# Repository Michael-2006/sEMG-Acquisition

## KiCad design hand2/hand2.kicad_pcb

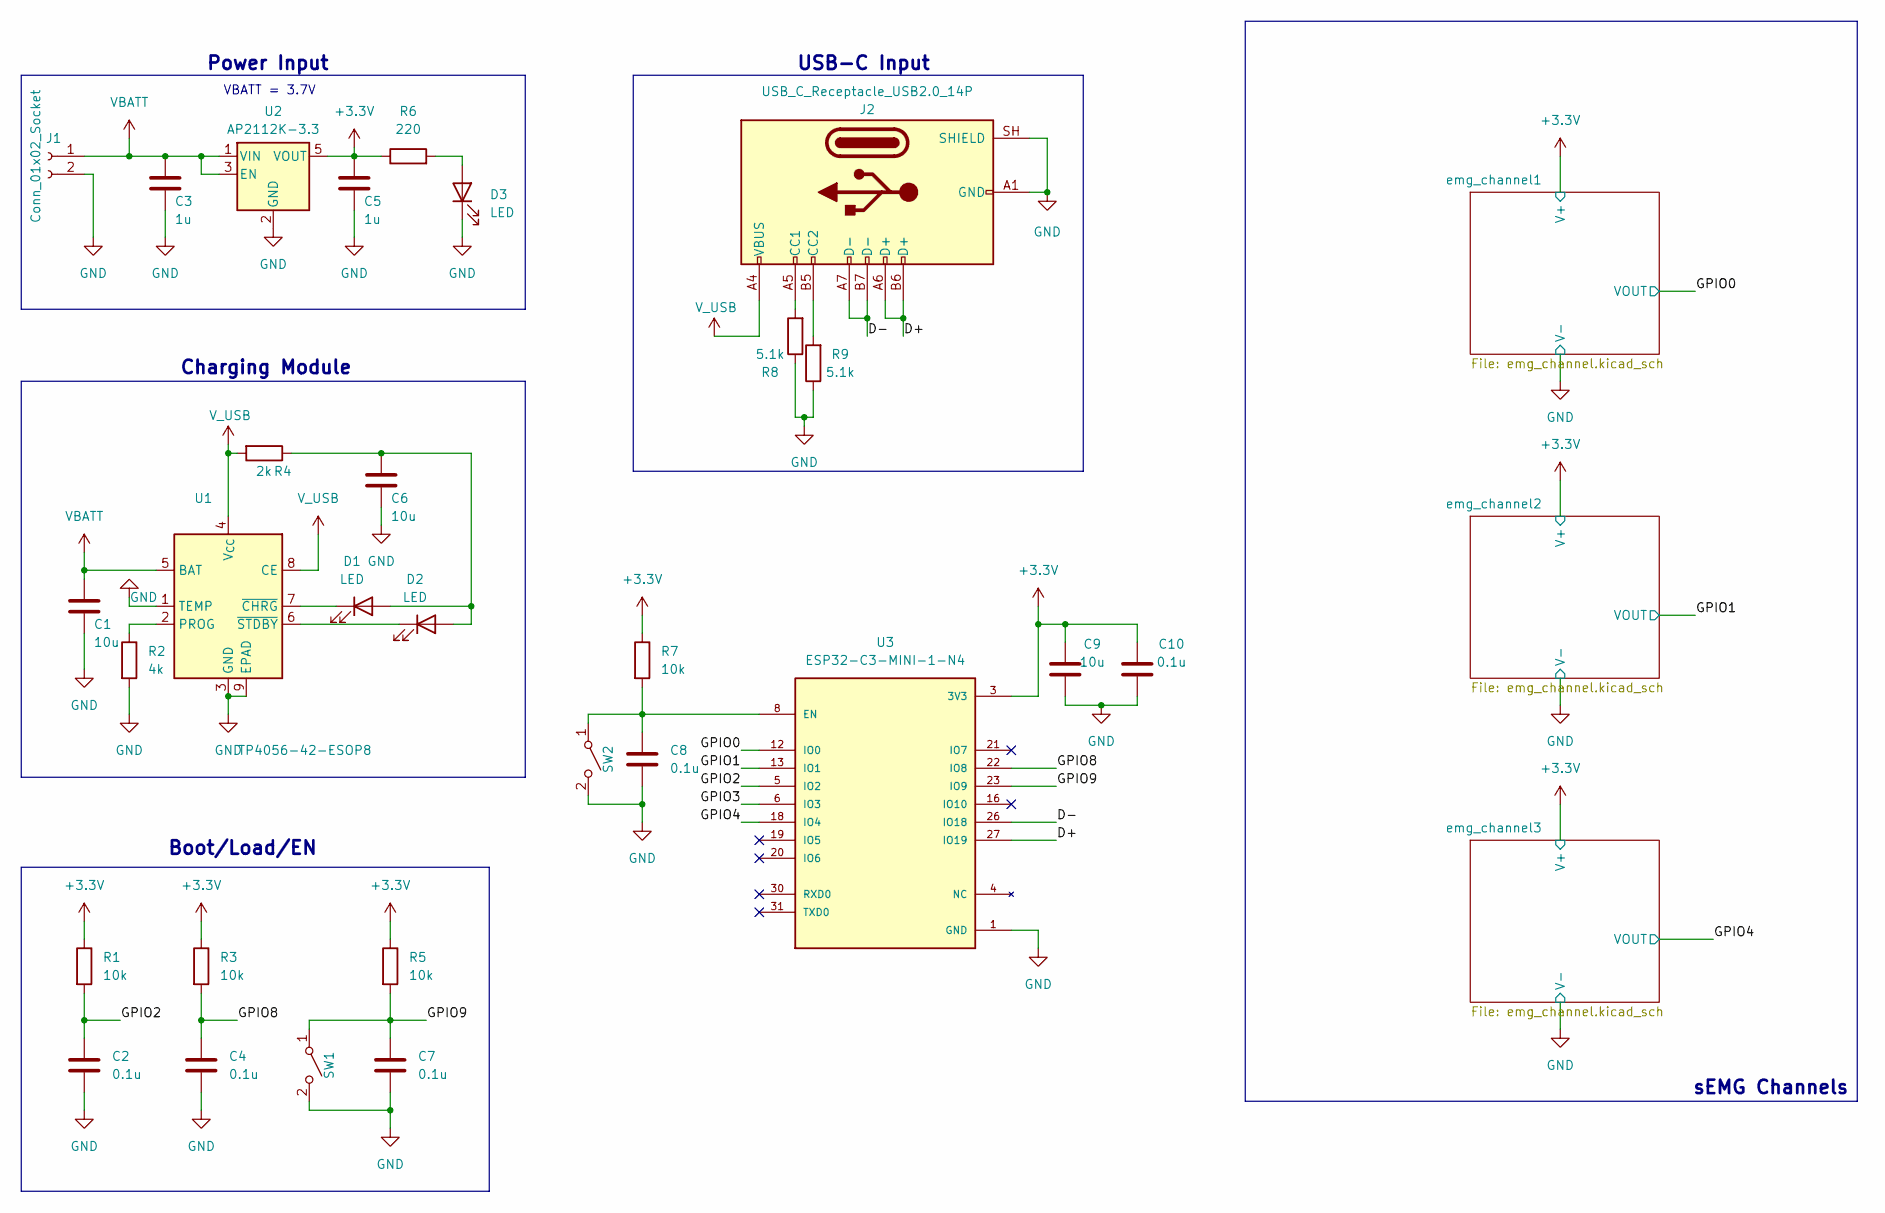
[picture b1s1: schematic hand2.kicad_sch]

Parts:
C1, C6, C9: 10u; C_0603_1608Metric_Pad1.08x0.95mm_HandSolder
C2, C4, C7, C8, C10: 0.1u; C_0603_1608Metric_Pad1.08x0.95mm_HandSolder
C3, C5: 1u; C_0603_1608Metric_Pad1.08x0.95mm_HandSolder
D1, D2, D3: LED; LED_0805_2012Metric_Pad1.15x1.40mm_HandSolder
J1: Conn_01x02_Socket; JST_PH_S2B-PH-SM4-TB_1x02-1MP_P2.00mm_Horizontal
J2: USB_C_Receptacle_USB2.0_14P; USB_C_Receptacle_HCTL_HC-TYPE-C-16P-01A
R1, R3, R5, R7: 10k; R_0603_1608Metric_Pad0.98x0.95mm_HandSolder
R2: 4k; R_0603_1608Metric_Pad0.98x0.95mm_HandSolder
R4: 2k; R_0603_1608Metric_Pad0.98x0.95mm_HandSolder
R6: 220; R_0603_1608Metric_Pad0.98x0.95mm_HandSolder
R8, R9: 5.1k; R_0603_1608Metric_Pad0.98x0.95mm_HandSolder
SW1, SW2: SW_SPST; SW_SPST_CK_RS282G05A3
U1: TP4056-42-ESOP8; SOIC-8-1EP_3.9x4.9mm_P1.27mm_EP2.41x3.3mm_ThermalVias
U2: AP2112K-3.3; SOT-23-5
U3: ESP32-C3-MINI-1-N4; XCVR_ESP32-C3-MINI-1-N4; PARTREV v1.0

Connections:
+3.3V: C5.1, C9.1, C10.2, R1.1, R3.1, R5.1, R6.1, R7.1, U2.5 (VOUT), U3.3 (3V3); also elsewhere on the board
/D+: J2.A6 (D+), J2.B6 (D+), U3.27 (IO19)
/D-: J2.A7 (D-), J2.B7 (D-), U3.26 (IO18)
/GPIO0: U3.12 (IO0); also elsewhere on the board
/GPIO1: U3.13 (IO1); also elsewhere on the board
/GPIO2: C2.1, R1.2, U3.5 (IO2)
/GPIO3: U3.6 (IO3)
/GPIO4: U3.18 (IO4); also elsewhere on the board
/GPIO8: C4.1, R3.2, U3.22 (IO8)
/GPIO9: C7.1, R5.2, SW1.1 (A), U3.23 (IO9)
unnamed: C6.1, D1.2 (A), D2.2 (A), R4.1
unnamed: D1.1 (K), U1.7 (~CHRG)
unnamed: D2.1 (K), U1.6 (~STDBY)
unnamed: D3.2 (A), R6.2
unnamed: J2.A5 (CC1), R8.2
unnamed: J2.B5 (CC2), R9.2
unnamed: C8.1, R7.2, SW2.1 (A), U3.8 (EN)
unnamed: R2.1, U1.2 (PROG)
VBATT: C1.1, C3.1, J1.1, U1.5 (BAT), U2.1 (VIN), U2.3 (EN)
V_USB: J2.A4 (VBUS), J2.A9 (VBUS), J2.B4 (VBUS), J2.B9 (VBUS), R4.2, U1.4 (V_{CC}), U1.8 (CE)

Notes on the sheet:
USB-C Input
VBATT = 3.7V
Power Input
Charging Module
Boot/Load/EN
sEMG Channels

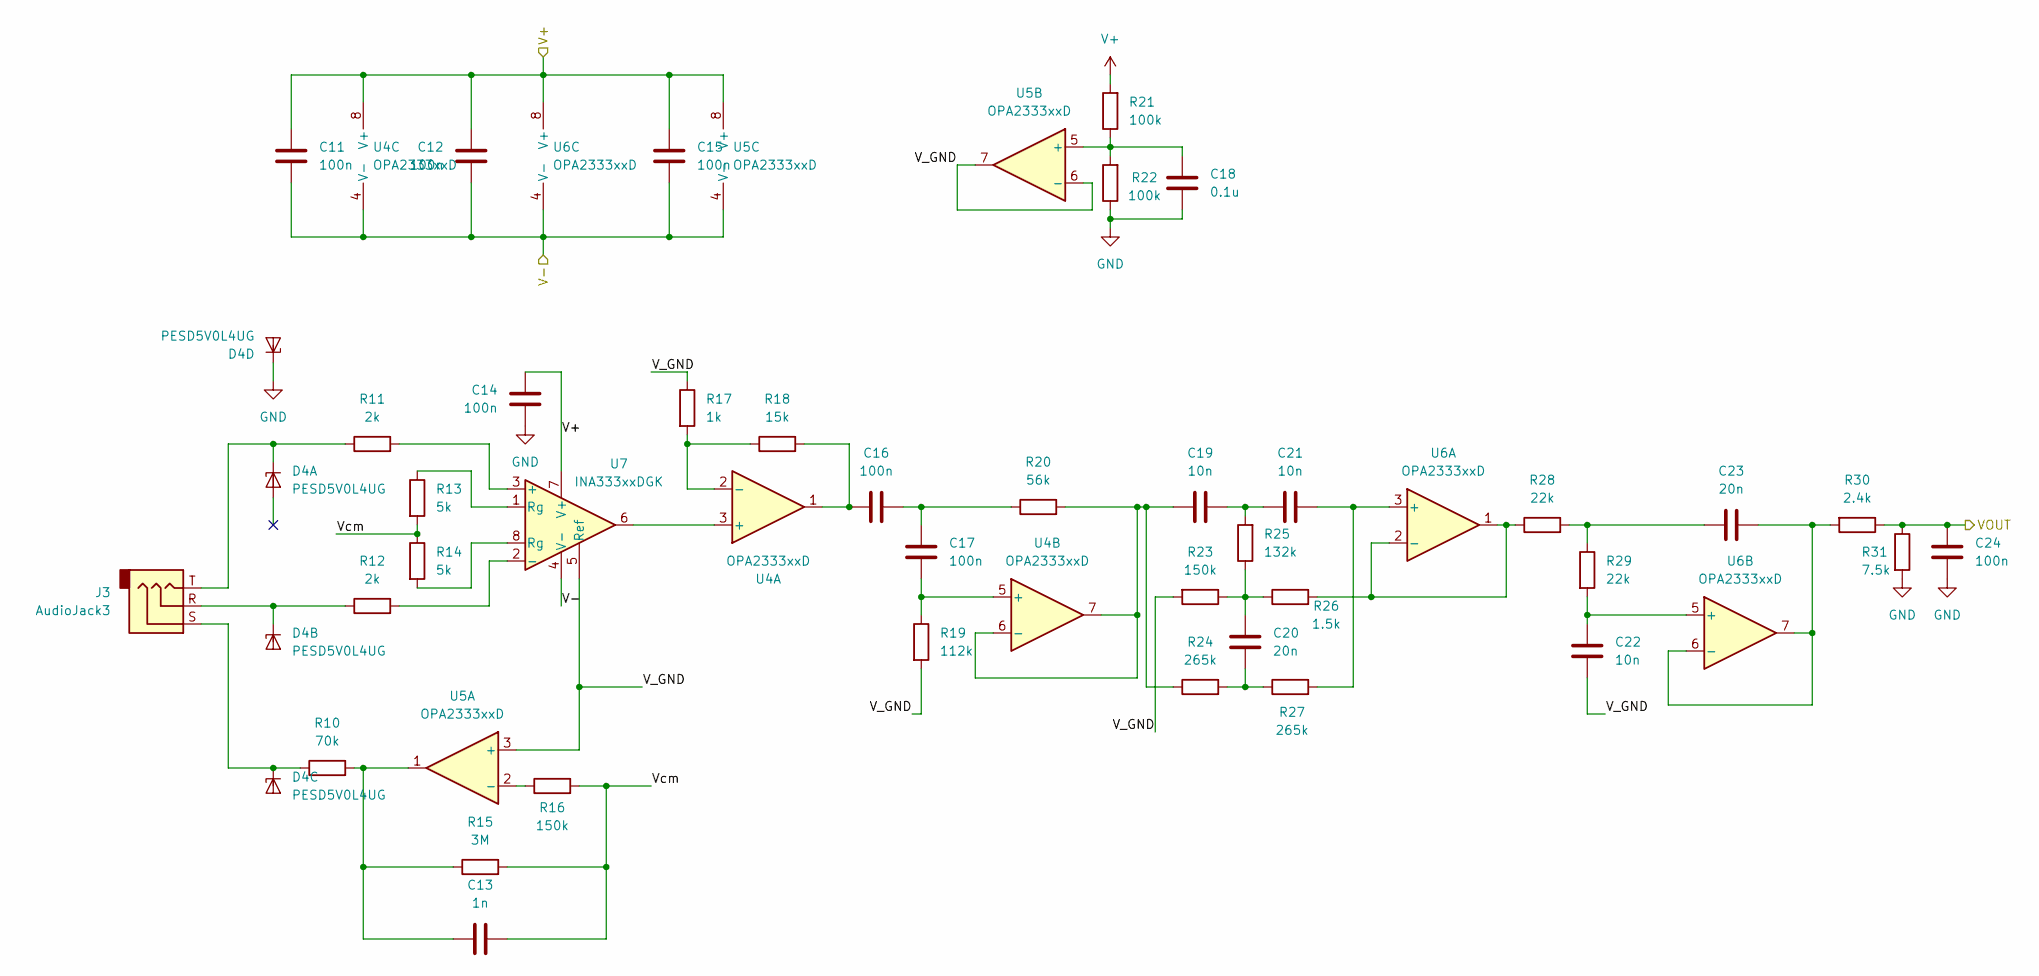
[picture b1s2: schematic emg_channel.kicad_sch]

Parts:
C11, C12, C14, C15, C16, C17, C24: 100n; C_0603_1608Metric_Pad1.08x0.95mm_HandSolder
C13: 1n; C_0603_1608Metric_Pad1.08x0.95mm_HandSolder
C18: 0.1u; C_0603_1608Metric_Pad1.08x0.95mm_HandSolder
C19, C21, C22: 10n; C_0603_1608Metric_Pad1.08x0.95mm_HandSolder
C20, C23: 20n; C_0603_1608Metric_Pad1.08x0.95mm_HandSolder
D4: PESD5V0L4UG; SOT-353_SC-70-5
J3: AudioJack3; Jack_3.5mm_CUI_SJ1-3533NG_Horizontal_CircularHoles
R10: 70k; R_0603_1608Metric_Pad0.98x0.95mm_HandSolder
R11, R12: 2k; R_0603_1608Metric_Pad0.98x0.95mm_HandSolder
R13, R14: 5k; R_0603_1608Metric_Pad0.98x0.95mm_HandSolder
R15: 3M; R_0603_1608Metric_Pad0.98x0.95mm_HandSolder
R16, R23: 150k; R_0603_1608Metric_Pad0.98x0.95mm_HandSolder
R17: 1k; R_0603_1608Metric_Pad0.98x0.95mm_HandSolder
R18: 15k; R_0603_1608Metric_Pad0.98x0.95mm_HandSolder
R19: 112k; R_0603_1608Metric_Pad0.98x0.95mm_HandSolder
R20: 56k; R_0603_1608Metric_Pad0.98x0.95mm_HandSolder
R21, R22: 100k; R_0603_1608Metric_Pad0.98x0.95mm_HandSolder
R24, R27: 265k; R_0603_1608Metric_Pad0.98x0.95mm_HandSolder
R25: 132k; R_0603_1608Metric_Pad0.98x0.95mm_HandSolder
R26: 1.5k; R_0603_1608Metric_Pad0.98x0.95mm_HandSolder
R28, R29: 22k; R_0603_1608Metric_Pad0.98x0.95mm_HandSolder
R30: 2.4k; R_0603_1608Metric_Pad0.98x0.95mm_HandSolder
R31: 7.5k; R_0603_1608Metric_Pad0.98x0.95mm_HandSolder
U4, U5, U6: OPA2333xxD; VSSOP-8_3x3mm_P0.65mm
U7: INA333xxDGK; VSSOP-8_3x3mm_P0.65mm

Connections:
+3.3V: C11.1, C12.1, C14.1, C15.1, R21.2, U4.8 (V+), U5.8 (V+), U6.8 (V+), U7.7 (V+); also elsewhere on the board
/GPIO0: C24.2, R30.1, R31.1; also elsewhere on the board
/emg_channel1/V_GND: C22.1, R17.1, R19.2, R23.2, U5.3 (+), U5.6 (-), U5.7, U7.5 (Ref)
/emg_channel1/Vcm: C13.1, R13.2, R14.1, R15.2, R16.2
unnamed: C13.2, R10.2, R15.1, U5.1
unnamed: C16.1, R18.2, U4.1
unnamed: C16.2, C17.1, R20.1
unnamed: C19.2, C21.1, R25.2
unnamed: C20.1, R24.2, R27.1
unnamed: C20.2, R23.1, R25.1, R26.1
unnamed: C23.1, R28.2, R29.1
unnamed: D4.1 (K1), J3.T, R11.1
unnamed: D4.3 (K2), J3.R, R12.1
unnamed: D4.4 (K3), J3.S, R10.1
unnamed: R13.1, U7.1 (Rg)
unnamed: R14.2, U7.8 (Rg)
unnamed: U4.3 (+), U7.6
unnamed: R17.2, R18.1, U4.2 (-)
unnamed: C17.2, R19.1, U4.5 (+)
unnamed: C19.1, R20.2, R24.1, U4.6 (-), U4.7
unnamed: R16.1, U5.2 (-)
unnamed: C18.1, R21.1, R22.2, U5.5 (+)
unnamed: C21.2, R27.2, U6.3 (+)
unnamed: R26.2, R28.1, U6.1, U6.2 (-)
unnamed: C22.2, R29.2, U6.5 (+)
unnamed: C23.2, R30.2, U6.6 (-), U6.7
unnamed: R11.2, U7.3 (+)
unnamed: R12.2, U7.2 (-)

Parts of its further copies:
C25, C26, C28, C29, C30, C31, C38, C39, C40, C42, C43, C44, C45, C52: 100n; C_0603_1608Metric_Pad1.08x0.95mm_HandSolder
C27, C41: 1n; C_0603_1608Metric_Pad1.08x0.95mm_HandSolder
C32, C46: 0.1u; C_0603_1608Metric_Pad1.08x0.95mm_HandSolder
C33, C35, C36, C47, C49, C50: 10n; C_0603_1608Metric_Pad1.08x0.95mm_HandSolder
C34, C37, C48, C51: 20n; C_0603_1608Metric_Pad1.08x0.95mm_HandSolder
D5, D6: PESD5V0L4UG; SOT-353_SC-70-5
J4, J5: AudioJack3; Jack_3.5mm_CUI_SJ1-3533NG_Horizontal_CircularHoles
R32, R54: 70k; R_0603_1608Metric_Pad0.98x0.95mm_HandSolder
R33, R34, R55, R56: 2k; R_0603_1608Metric_Pad0.98x0.95mm_HandSolder
R35, R36, R57, R58: 5k; R_0603_1608Metric_Pad0.98x0.95mm_HandSolder
R37, R59: 3M; R_0603_1608Metric_Pad0.98x0.95mm_HandSolder
R38, R45, R60, R67: 150k; R_0603_1608Metric_Pad0.98x0.95mm_HandSolder
R39, R61: 1k; R_0603_1608Metric_Pad0.98x0.95mm_HandSolder
R40, R62: 15k; R_0603_1608Metric_Pad0.98x0.95mm_HandSolder
R41, R63: 112k; R_0603_1608Metric_Pad0.98x0.95mm_HandSolder
R42, R64: 56k; R_0603_1608Metric_Pad0.98x0.95mm_HandSolder
R43, R44, R65, R66: 100k; R_0603_1608Metric_Pad0.98x0.95mm_HandSolder
R46, R49, R68, R71: 265k; R_0603_1608Metric_Pad0.98x0.95mm_HandSolder
R47, R69: 132k; R_0603_1608Metric_Pad0.98x0.95mm_HandSolder
R48, R70: 1.5k; R_0603_1608Metric_Pad0.98x0.95mm_HandSolder
R50, R51, R72, R73: 22k; R_0603_1608Metric_Pad0.98x0.95mm_HandSolder
R52, R74: 2.4k; R_0603_1608Metric_Pad0.98x0.95mm_HandSolder
R53, R75: 7.5k; R_0603_1608Metric_Pad0.98x0.95mm_HandSolder
U8, U9, U10, U12, U13, U14: OPA2333xxD; VSSOP-8_3x3mm_P0.65mm
U11, U15: INA333xxDGK; VSSOP-8_3x3mm_P0.65mm

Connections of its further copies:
+3.3V: C25.1, C26.1, C28.1, C29.1, C39.1, C40.1, C42.1, C43.1, R43.2, R65.2, U8.8 (V+), U9.8 (V+), U10.8 (V+), U11.7 (V+), U12.8 (V+), U13.8 (V+), U14.8 (V+), U15.7 (V+); also elsewhere on the board
/GPIO1: C38.2, R52.1, R53.1; also elsewhere on the board
/GPIO4: C52.2, R74.1, R75.1; also elsewhere on the board
/emg_channel2/V_GND: C36.1, R39.1, R41.2, R45.2, U9.3 (+), U9.6 (-), U9.7, U11.5 (Ref)
/emg_channel2/Vcm: C27.1, R35.2, R36.1, R37.2, R38.2
/emg_channel3/V_GND: C50.1, R61.1, R63.2, R67.2, U13.3 (+), U13.6 (-), U13.7, U15.5 (Ref)
/emg_channel3/Vcm: C41.1, R57.2, R58.1, R59.2, R60.2
unnamed: C27.2, R32.2, R37.1, U9.1
unnamed: C30.1, R40.2, U8.1
unnamed: C30.2, C31.1, R42.1
unnamed: C33.2, C35.1, R47.2
unnamed: C34.1, R46.2, R49.1
unnamed: C34.2, R45.1, R47.1, R48.1
unnamed: C37.1, R50.2, R51.1
unnamed: C41.2, R54.2, R59.1, U13.1
unnamed: C44.1, R62.2, U12.1
unnamed: C44.2, C45.1, R64.1
unnamed: C47.2, C49.1, R69.2
unnamed: C48.1, R68.2, R71.1
unnamed: C48.2, R67.1, R69.1, R70.1
unnamed: C51.1, R72.2, R73.1
unnamed: D5.1 (K1), J4.T, R33.1
unnamed: D5.3 (K2), J4.R, R34.1
unnamed: D5.4 (K3), J4.S, R32.1
unnamed: D6.1 (K1), J5.T, R55.1
unnamed: D6.3 (K2), J5.R, R56.1
unnamed: D6.4 (K3), J5.S, R54.1
unnamed: R35.1, U11.1 (Rg)
unnamed: R36.2, U11.8 (Rg)
unnamed: R57.1, U15.1 (Rg)
unnamed: R58.2, U15.8 (Rg)
unnamed: U8.3 (+), U11.6
unnamed: R39.2, R40.1, U8.2 (-)
unnamed: C31.2, R41.1, U8.5 (+)
unnamed: C33.1, R42.2, R46.1, U8.6 (-), U8.7
unnamed: R38.1, U9.2 (-)
unnamed: C32.1, R43.1, R44.2, U9.5 (+)
unnamed: C35.2, R49.2, U10.3 (+)
unnamed: R48.2, R50.1, U10.1, U10.2 (-)
unnamed: C36.2, R51.2, U10.5 (+)
unnamed: C37.2, R52.2, U10.6 (-), U10.7
unnamed: R33.2, U11.3 (+)
unnamed: R34.2, U11.2 (-)
unnamed: U12.3 (+), U15.6
unnamed: R61.2, R62.1, U12.2 (-)
unnamed: C45.2, R63.1, U12.5 (+)
unnamed: C47.1, R64.2, R68.1, U12.6 (-), U12.7
unnamed: R60.1, U13.2 (-)
unnamed: C46.1, R65.1, R66.2, U13.5 (+)
unnamed: C49.2, R71.2, U14.3 (+)
unnamed: R70.2, R72.1, U14.1, U14.2 (-)
unnamed: C50.2, R73.2, U14.5 (+)
unnamed: C51.2, R74.2, U14.6 (-), U14.7
unnamed: R55.2, U15.3 (+)
unnamed: R56.2, U15.2 (-)

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
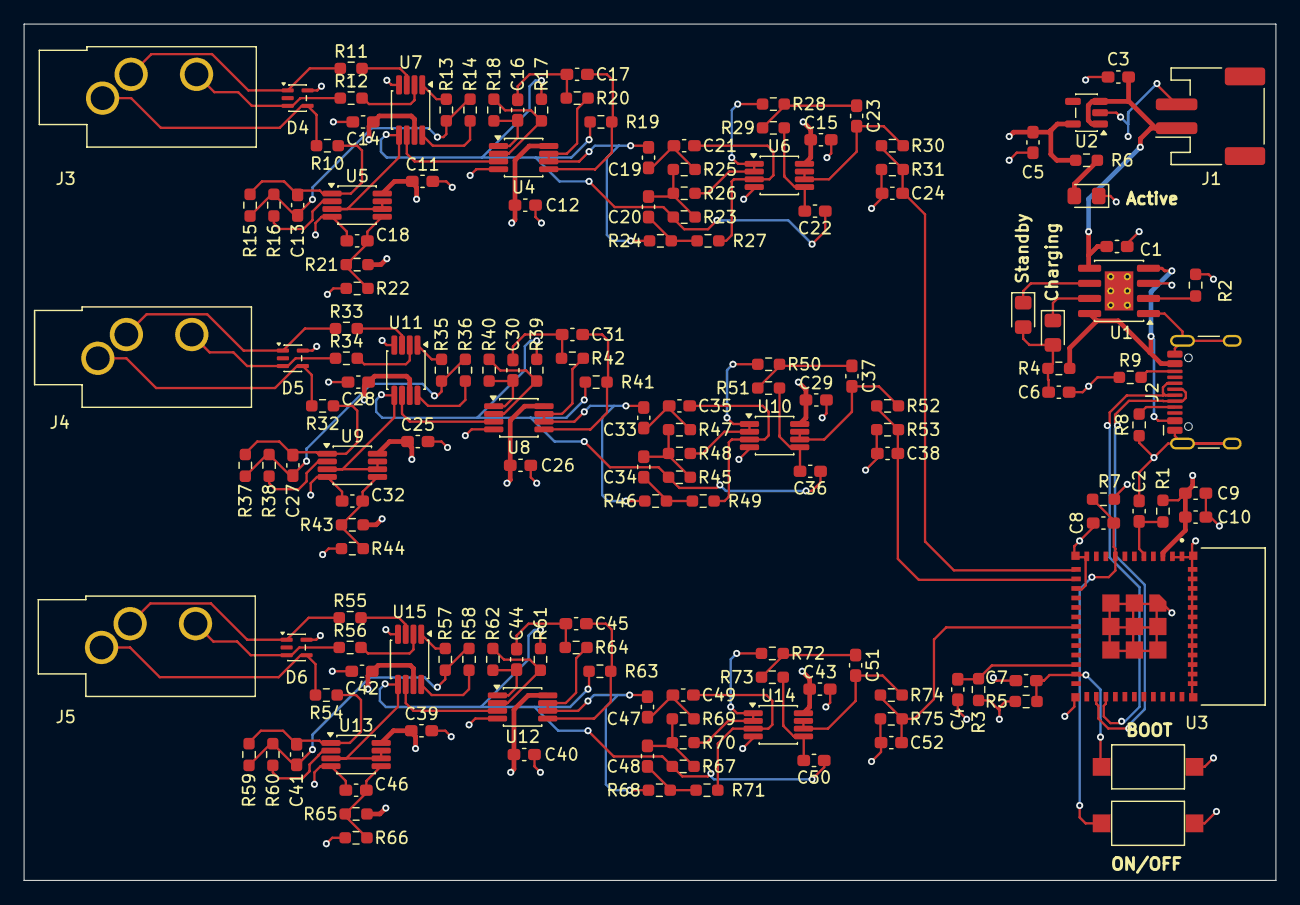
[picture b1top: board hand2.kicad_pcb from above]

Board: 4 copper layers, 105.2 x 72.0 mm, 155 parts (0 on the bottom side), 98 nets.
